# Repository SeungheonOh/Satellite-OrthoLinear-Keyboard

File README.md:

# Satellite OrthoLinear Keyboard

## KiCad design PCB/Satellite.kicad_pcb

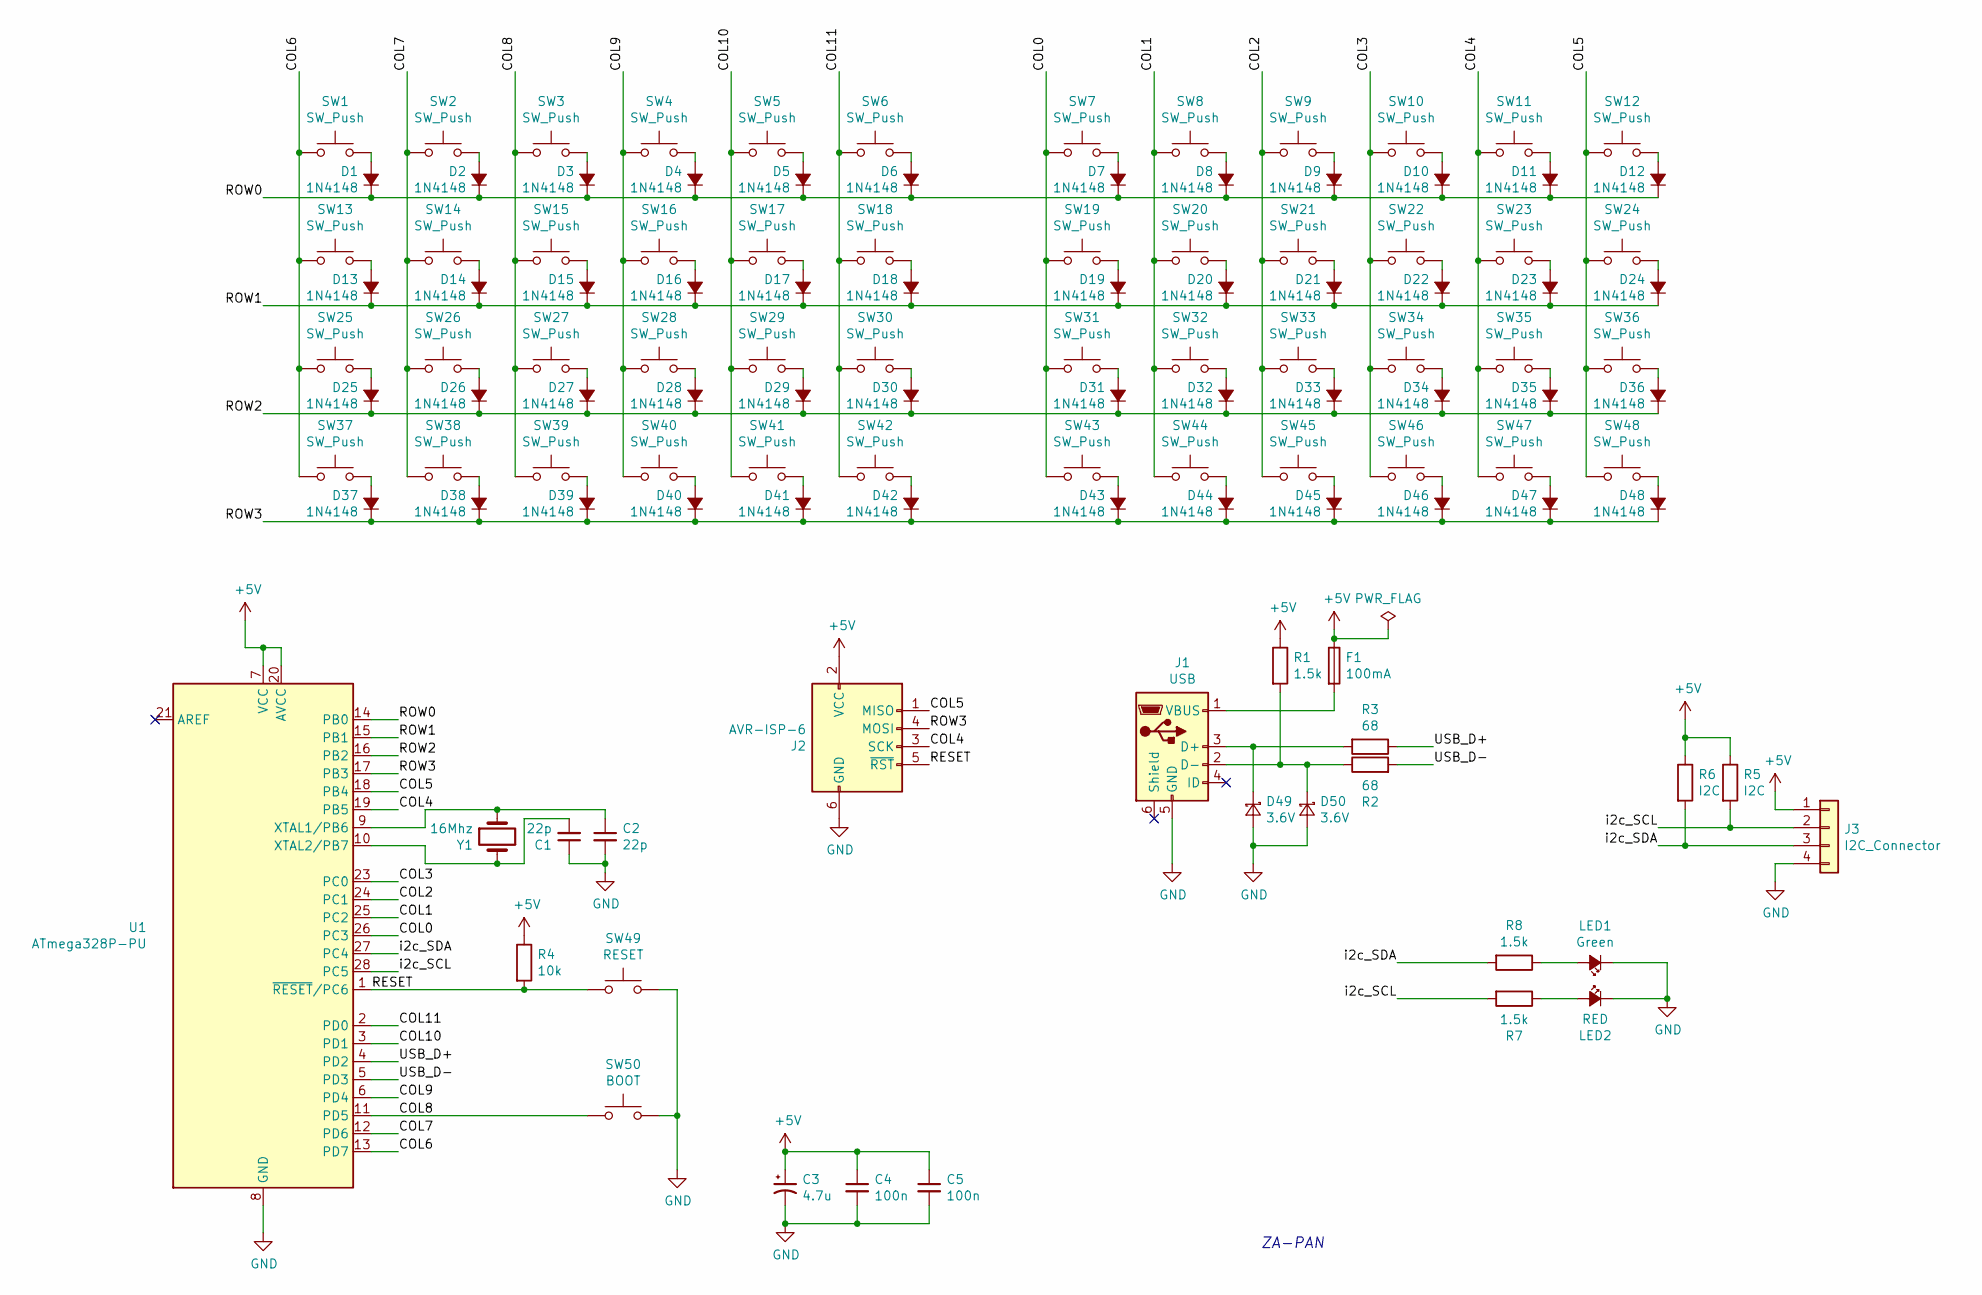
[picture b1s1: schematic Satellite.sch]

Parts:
C1, C2: 22p; C_Disc_D3.4mm_W2.1mm_P2.50mm
C3: 4.7u; CP_Radial_D4.0mm_P1.50mm
C4, C5: 100n; C_Disc_D6.0mm_W2.5mm_P5.00mm
D1, D2, D3, D4, D5, D6, D7, D8, D9, D10, D11, D12, D13, D14, D15, D16, D17, D18, D19, D20, D21, D22, D23, D24, D25, D26, D27, D28, D29, D30, D31, D32, D33, D34, D35, D36, D37, D38, D39, D40, D41, D42, D43, D44, D45, D46, D47, D48: 1N4148; D_DO-35_SOD27_P7.62mm_Horizontal
D49, D50: 3.6V; D_DO-35_SOD27_P7.62mm_Horizontal
F1: 100mA; Fuse_BelFuse_0ZRE0005FF_L8.3mm_W3.8mm
J1: USB; USB_Mini-B_Tensility_54-00023_Vertical
J2: AVR-ISP-6; IDC-Header_2x03_P2.54mm_Vertical
J3: I2C_Connector; SolderWirePad_1x04_P3.175mm_Drill0.8mm
LED1: Green; LED_D3.0mm
LED2: RED; LED_D3.0mm
R1, R7, R8: 1.5k; R_Axial_DIN0309_L9.0mm_D3.2mm_P12.70mm_Horizontal
R2, R3: 68; R_Axial_DIN0309_L9.0mm_D3.2mm_P12.70mm_Horizontal
R4: 10k; R_Axial_DIN0309_L9.0mm_D3.2mm_P12.70mm_Horizontal
R5, R6: I2C; R_Axial_DIN0309_L9.0mm_D3.2mm_P12.70mm_Horizontal
SW1, SW2, SW3, SW4, SW5, SW6, SW7, SW8, SW9, SW10, SW12, SW13, SW14, SW15, SW16, SW17, SW18, SW19, SW20, SW21, SW22, SW23, SW24, SW25, SW26, SW27, SW28, SW29, SW30, SW31, SW32, SW33, SW34, SW35, SW36, SW37, SW38, SW39, SW40, SW41, SW42, SW43, SW44, SW45, SW46, SW47, SW48: SW_Push; SW_Cherry_MX_1.00u_PCB
SW11: SW_Push; MX-1U-NoLED
SW49: RESET; SW_PUSH_6mm
SW50: BOOT; SW_PUSH_6mm
U1: ATmega328P-PU; DIP-28_W7.62mm_Socket
Y1: 16Mhz; Crystal_HC49-4H_Vertical

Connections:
+5V: C3.1, C4.1, C5.1, F1.1, J2.2 (VCC), J3.1, R1.1, R4.1, R5.1, R6.1, U1.7 (VCC), U1.20 (AVCC); also elsewhere on the board
/COL0: SW7.2, SW19.2, SW31.2, SW43.2, U1.26 (PC3); also elsewhere on the board
/COL1: SW8.2, SW20.2, SW32.2, SW44.2, U1.25 (PC2); also elsewhere on the board
/COL2: SW9.2, SW21.2, SW33.2, SW45.2, U1.24 (PC1); also elsewhere on the board
/COL3: SW10.2, SW22.2, SW34.2, SW46.2, U1.23 (PC0); also elsewhere on the board
/COL4: J2.3 (SCK), SW11.2, SW23.2, SW35.2, SW47.2, U1.19 (PB5); also elsewhere on the board
/COL5: J2.1 (MISO), SW12.2, SW24.2, SW36.2, SW48.2, U1.18 (PB4); also elsewhere on the board
/COL6: SW1.2, SW13.2, SW25.2, SW37.2, U1.13 (PD7); also elsewhere on the board
/COL7: SW2.2, SW14.2, SW26.2, SW38.2, U1.12 (PD6); also elsewhere on the board
/COL8: SW3.2, SW15.2, SW27.2, SW39.2, SW50.2, U1.11 (PD5); also elsewhere on the board
/COL9: SW4.2, SW16.2, SW28.2, SW40.2, U1.6 (PD4); also elsewhere on the board
/COL10: SW5.2, SW17.2, SW29.2, SW41.2, U1.3 (PD1); also elsewhere on the board
/COL11: SW6.2, SW18.2, SW30.2, SW42.2, U1.2 (PD0); also elsewhere on the board
/RESET: J2.5 (~RST), R4.2, SW49.2, U1.1 (~RESET~/PC6); also elsewhere on the board
/ROW0: D1.1 (K), D2.1 (K), D3.1 (K), D4.1 (K), D5.1 (K), D6.1 (K), D7.1 (K), D8.1 (K), D9.1 (K), D10.1 (K), D11.1 (K), D12.1 (K), U1.14 (PB0); also elsewhere on the board
/ROW1: D13.1 (K), D14.1 (K), D15.1 (K), D16.1 (K), D17.1 (K), D18.1 (K), D19.1 (K), D20.1 (K), D21.1 (K), D22.1 (K), D23.1 (K), D24.1 (K), U1.15 (PB1); also elsewhere on the board
/ROW2: D25.1 (K), D26.1 (K), D27.1 (K), D28.1 (K), D29.1 (K), D30.1 (K), D31.1 (K), D32.1 (K), D33.1 (K), D34.1 (K), D35.1 (K), D36.1 (K), U1.16 (PB2); also elsewhere on the board
/ROW3: D37.1 (K), D38.1 (K), D39.1 (K), D40.1 (K), D41.1 (K), D42.1 (K), D43.1 (K), D44.1 (K), D45.1 (K), D46.1 (K), D47.1 (K), D48.1 (K), J2.4 (MOSI), U1.17 (PB3); also elsewhere on the board
/USB_D+: R3.1, U1.4 (PD2); also elsewhere on the board
/USB_D-: R2.2, U1.5 (PD3); also elsewhere on the board
/i2c_SCL: J3.2, R5.2, R7.2, U1.28 (PC5); also elsewhere on the board
/i2c_SDA: J3.3, R6.2, R8.2, U1.27 (PC4); also elsewhere on the board
GND: C1.1, C2.2, C3.2, C4.2, C5.2, D49.2 (A), D50.2 (A), J1.4 (ID), J1.5 (GND), J2.6 (GND), J3.4, LED1.1 (K), LED2.1 (K), SW49.1, SW50.1, U1.8 (GND), U1.22 (GND); also elsewhere on the board
unnamed 23: C1.2, U1.10 (XTAL2/PB7), Y1.2; also elsewhere on the board
unnamed 24: C2.1, U1.9 (XTAL1/PB6), Y1.1; also elsewhere on the board
unnamed: D1.2 (A), SW1.1
unnamed: D2.2 (A), SW2.1
unnamed: D3.2 (A), SW3.1
unnamed: D4.2 (A), SW4.1
unnamed: D5.2 (A), SW5.1
unnamed: D6.2 (A), SW6.1
unnamed: D7.2 (A), SW7.1
unnamed: D8.2 (A), SW8.1
unnamed: D9.2 (A), SW9.1
unnamed: D10.2 (A), SW10.1
unnamed: D11.2 (A), SW11.1
unnamed: D12.2 (A), SW12.1
unnamed: D13.2 (A), SW13.1
unnamed: D14.2 (A), SW14.1
unnamed: D15.2 (A), SW15.1
unnamed: D16.2 (A), SW16.1
unnamed: D17.2 (A), SW17.1
unnamed: D18.2 (A), SW18.1
unnamed: D19.2 (A), SW19.1
unnamed: D20.2 (A), SW20.1
unnamed: D21.2 (A), SW21.1
unnamed: D22.2 (A), SW22.1
unnamed: D23.2 (A), SW23.1
unnamed: D24.2 (A), SW24.1
unnamed: D25.2 (A), SW25.1
unnamed: D26.2 (A), SW26.1
unnamed: D27.2 (A), SW27.1
unnamed: D28.2 (A), SW28.1
unnamed: D29.2 (A), SW29.1
unnamed: D30.2 (A), SW30.1
unnamed: D31.2 (A), SW31.1
unnamed: D32.2 (A), SW32.1
unnamed: D33.2 (A), SW33.1
unnamed: D34.2 (A), SW34.1
unnamed: D35.2 (A), SW35.1
unnamed: D36.2 (A), SW36.1
unnamed: D37.2 (A), SW37.1
unnamed: D38.2 (A), SW38.1
unnamed: D39.2 (A), SW39.1
unnamed: D40.2 (A), SW40.1
unnamed: D41.2 (A), SW41.1
unnamed: D42.2 (A), SW42.1
unnamed: D43.2 (A), SW43.1
unnamed: D44.2 (A), SW44.1
unnamed: D45.2 (A), SW45.1
unnamed: D46.2 (A), SW46.1
unnamed: D47.2 (A), SW47.1
unnamed: D48.2 (A), SW48.1
unnamed: F1.2, J1.1 (VBUS)
unnamed 74: LED1.2 (A), R8.1; also elsewhere on the board
unnamed 75: LED2.2 (A), R7.1; also elsewhere on the board

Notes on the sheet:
ZA-PAN

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
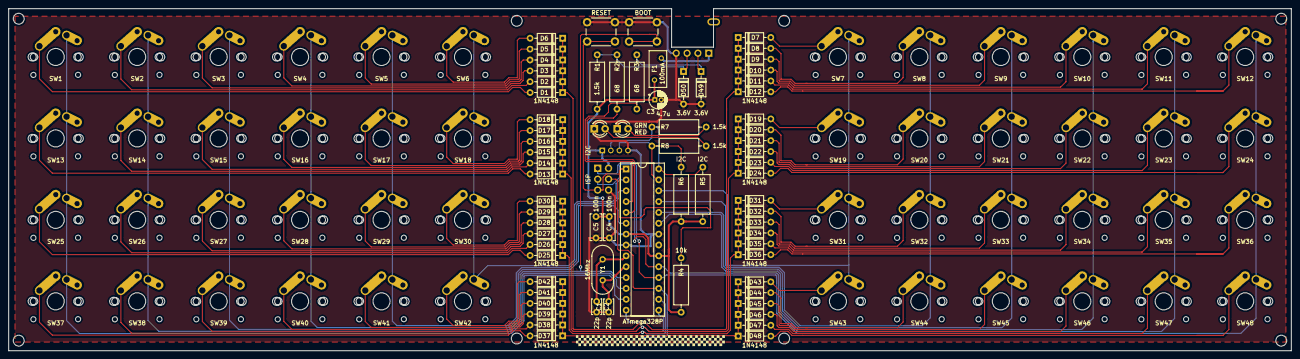
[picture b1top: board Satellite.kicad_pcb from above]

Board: 2 copper layers, 300.0 x 80.0 mm, 121 parts (0 on the bottom side), 78 nets.

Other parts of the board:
ATmega328P: ATmega328P-PU; DIP-28_W7.62mm_Socket
BOOT: BOOT; SW_PUSH_6mm
GRN: Green; LED_D3.0mm
I2C: I2C_Connector; PinHeader_1x04_P2.00mm_Vertical
ISP: AVR-ISP-6; IDC-Header_2x03_P2.54mm_Vertical
RED: RED; LED_D3.0mm
RESET: RESET; SW_PUSH_6mm

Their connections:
+5V: ATmega328P.7, ATmega328P.20, I2C.1, ISP.2; also elsewhere on the board
/COL0: ATmega328P.26; also elsewhere on the board
/COL1: ATmega328P.25; also elsewhere on the board
/COL2: ATmega328P.24; also elsewhere on the board
/COL3: ATmega328P.23; also elsewhere on the board
/COL4: ATmega328P.19, ISP.3; also elsewhere on the board
/COL5: ATmega328P.18, ISP.1; also elsewhere on the board
/COL6: ATmega328P.13; also elsewhere on the board
/COL7: ATmega328P.12; also elsewhere on the board
/COL8: ATmega328P.11, BOOT.2; also elsewhere on the board
/COL9: ATmega328P.6; also elsewhere on the board
/COL10: ATmega328P.3; also elsewhere on the board
/COL11: ATmega328P.2; also elsewhere on the board
/RESET: ATmega328P.1, ISP.5, RESET.2; also elsewhere on the board
/ROW0: ATmega328P.14; also elsewhere on the board
/ROW1: ATmega328P.15; also elsewhere on the board
/ROW2: ATmega328P.16; also elsewhere on the board
/ROW3: ATmega328P.17, ISP.4; also elsewhere on the board
/USB_D+: ATmega328P.4; also elsewhere on the board
/USB_D-: ATmega328P.5; also elsewhere on the board
/i2c_SCL: ATmega328P.28, I2C.2; also elsewhere on the board
/i2c_SDA: ATmega328P.27, I2C.3; also elsewhere on the board
GND: ATmega328P.8, ATmega328P.22, BOOT.1, GRN.1, I2C.4, ISP.6, RED.1, RESET.1; also elsewhere on the board
unnamed 23: ATmega328P.10; also elsewhere on the board
unnamed 24: ATmega328P.9; also elsewhere on the board
unnamed 74: GRN.2; also elsewhere on the board
unnamed 75: RED.2; also elsewhere on the board

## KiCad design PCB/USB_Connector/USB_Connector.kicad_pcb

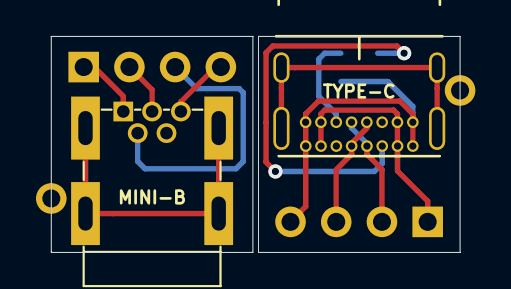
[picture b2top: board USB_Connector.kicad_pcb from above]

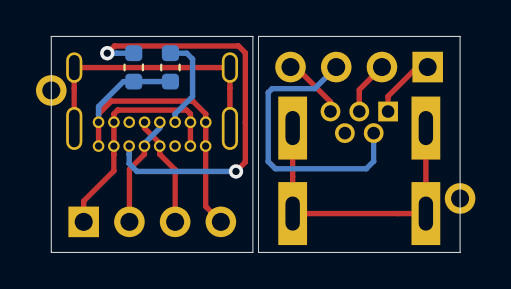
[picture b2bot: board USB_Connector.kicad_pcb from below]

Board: 2 copper layers, 22.7 x 12.0 mm, 6 parts (2 on the bottom side), 10 nets.

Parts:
J1, J2: Conn_01x04_MountingPin; PinHeader_1x04_P2.54mm_Vertical
MINI-B: USB_B_Mini; USB_Mini-B_THT_Horizontal
R1, R1#2: 5.1k; R_0603_1608Metric
TYPE-C: USB_C_Plug_USB2.0; USB_C_GCT_USB4085

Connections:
/GND: J1.4, R1.1, R1#2.1, TYPE-C.A1, TYPE-C.A12, TYPE-C.B1, TYPE-C.B12
unnamed: J1.1, TYPE-C.A4, TYPE-C.A9, TYPE-C.B4, TYPE-C.B9
unnamed: J1.2, TYPE-C.A6, TYPE-C.B6
unnamed: J1.3, TYPE-C.A7, TYPE-C.B7
unnamed: J2.1, MINI-B.1
unnamed: J2.2, MINI-B.3
unnamed: J2.3, MINI-B.2
unnamed: J2.4, MINI-B.5
unnamed: R1#2.2, TYPE-C.A5
unnamed: R1.2, TYPE-C.B5

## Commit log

2019-05-18 Hybrid Socket upgrade
2019-05-18 PCB minor
2019-05-18 Minor
2019-05-20 USB connecters
2019-05-24 3D Models(WRL files)
2019-05-25 BackPlate
2019-05-31 Choc_MX
2019-05-31 Minor update
